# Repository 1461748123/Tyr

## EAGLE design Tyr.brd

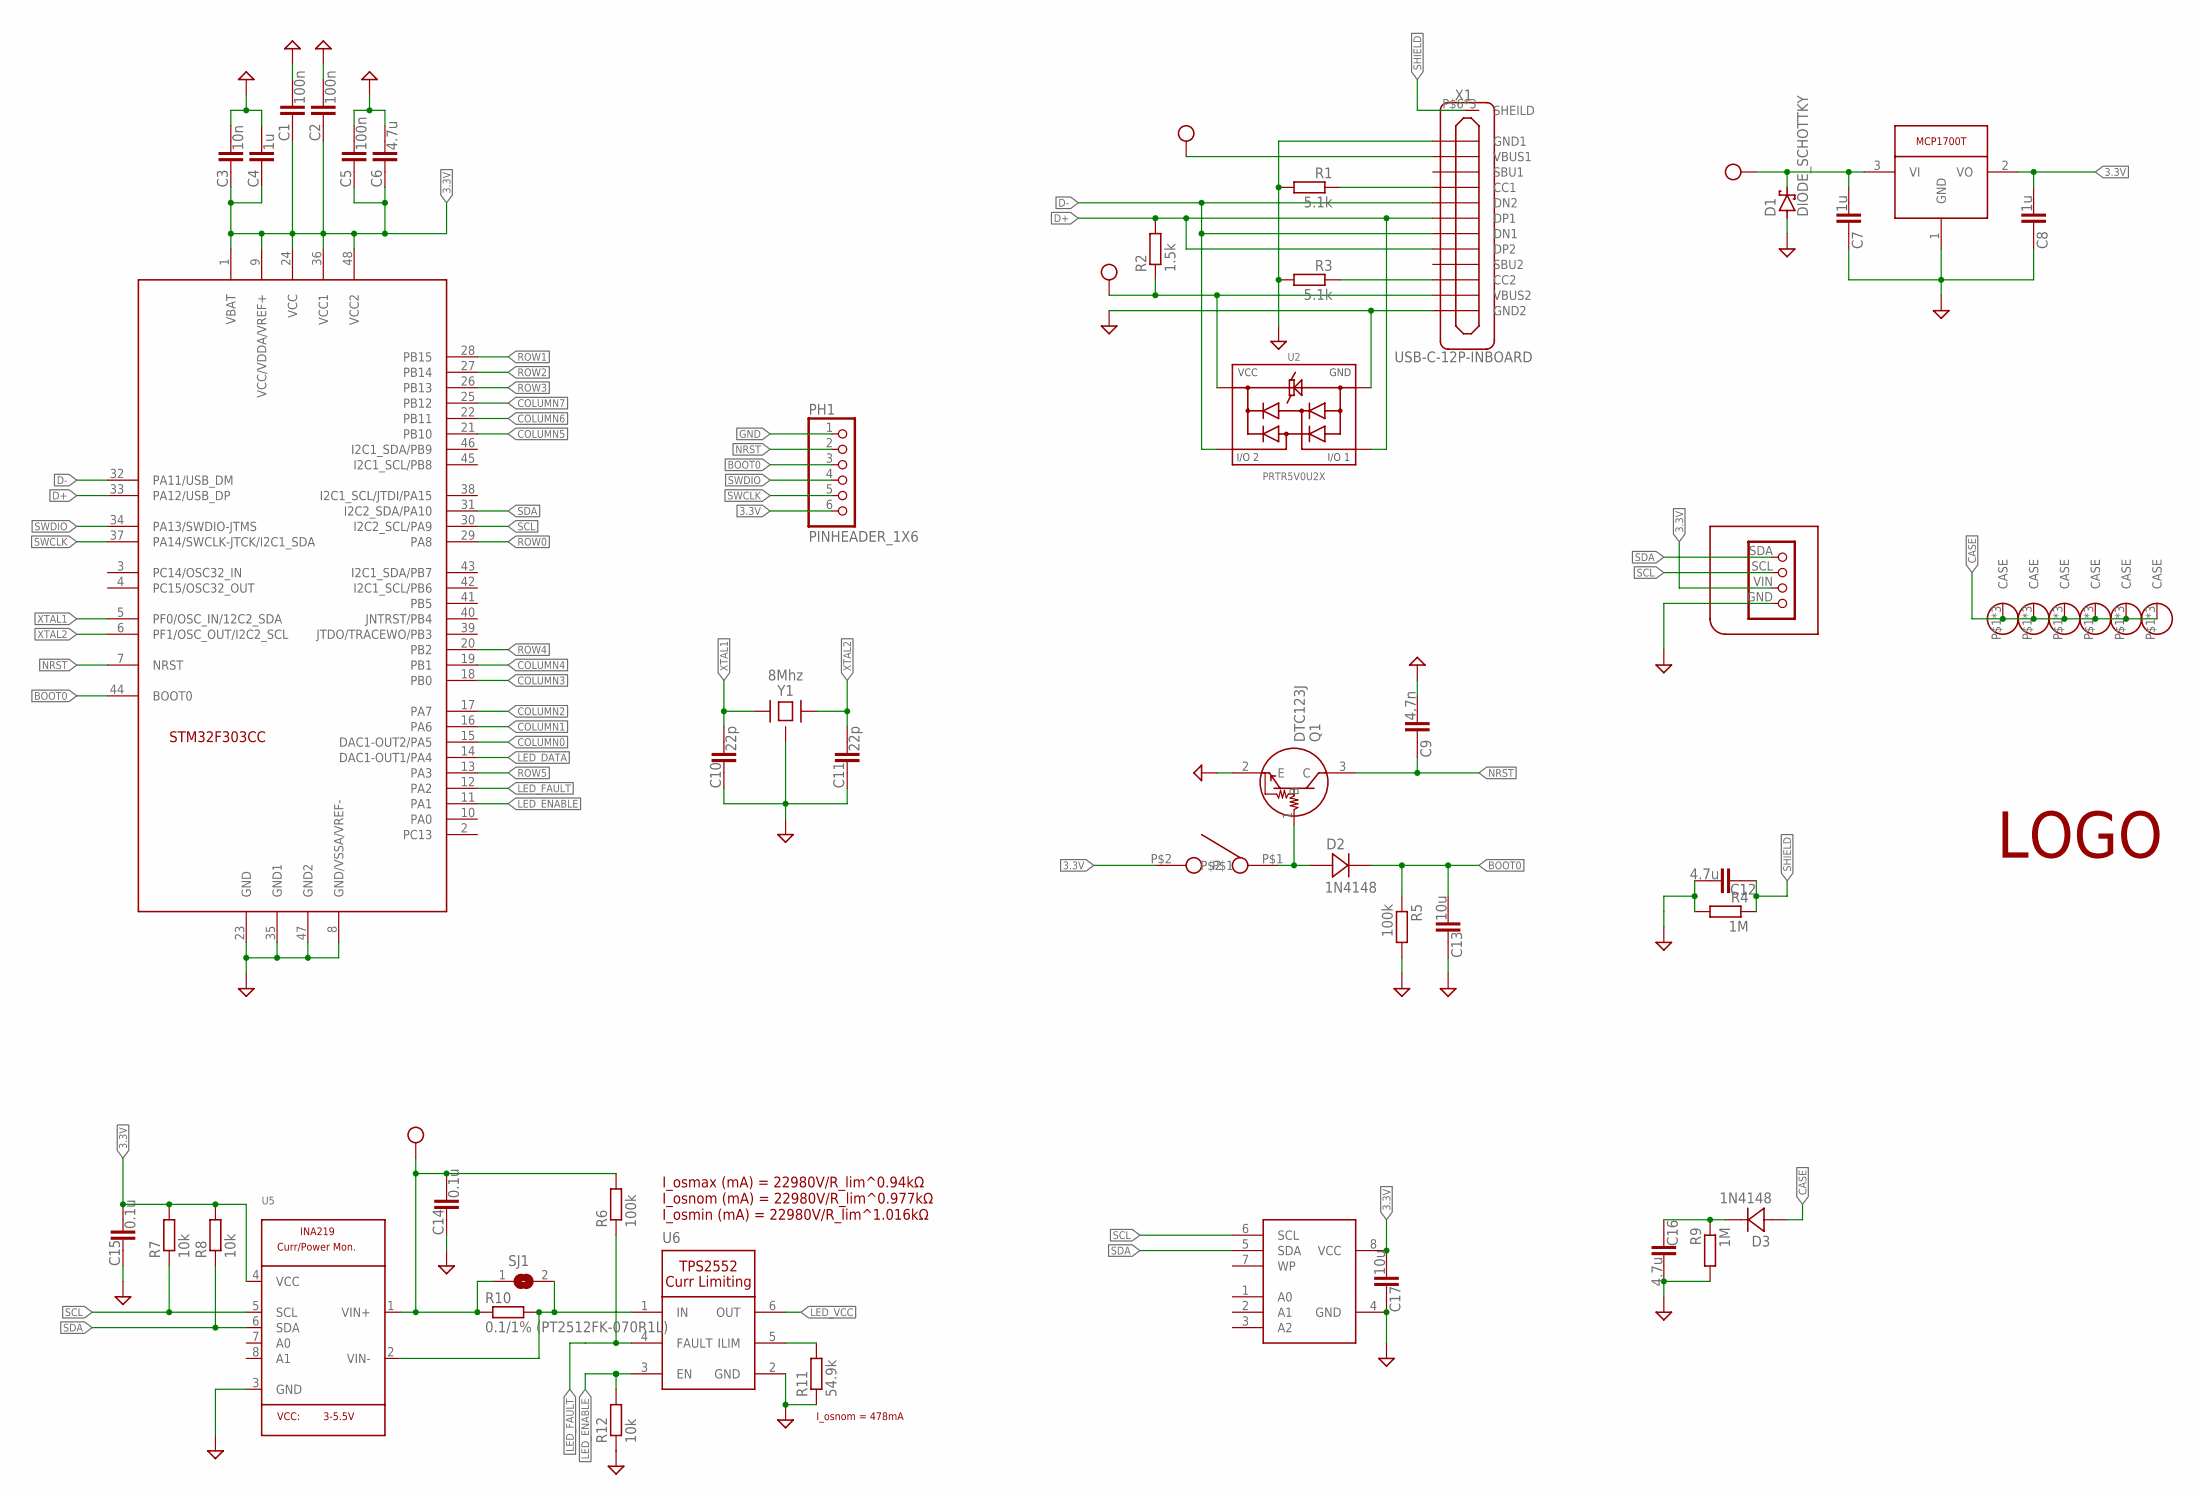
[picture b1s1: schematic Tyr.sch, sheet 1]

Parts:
C1, C2, C5: 100n; C0603
C3: 10n; C0603
C4, C7, C8: 1u; C0603
C6, C12, C16: 4.7u; C0603
C9: 4.7n; C0603
C10, C11: 22p; C0603
C13, C17: 10u; C0603
C14, C15: 0.1u; C0603
D1: DIODE_SCHOTTKY; SOD-123
D2, D3: 1N4148; SOD-123
HOLE1, HOLE2: MOUNT_HOLE-5MM_NOTCH; HOLE_5MM_OVAL
HOLE3, HOLE4, HOLE5, HOLE6: MOUNT_HOLE; HOLE_M3_OVAL
J1: TYR_DISPLAY; TYR_TYR_DISPLAY
LOGO1: LOGO_TYR; LOGO_TYR_COPPER
PH1: PINHEADER_1X6; 1X06
Q1: DTC123J; SOT-323
R1, R3: 5.1k; R0603
R2: 1.5k; R0603
R4, R9: 1M; R0603
R5, R6: 100k; R0603
R7, R8, R12: 10k; R0603
R10: 0.1/1% (PT2512FK-070R1L); R2512
R11: 54.9k; R0603
SJ1: SOLDERJUMPER; SOLDERJUMPER_ARROW_NOPASTE
SW1: BUTTON; BUTTON_3*6*2.5
U1: MCP1700T; SOT-23
U2: PRTR5V0U2X
U3: STM32F303CC; LQFP48
U4: MB85RC256V; SOP-8
U5: INA219; SOT23-8
U6: TPS2552; SOT-23-6P
X1: USB-C-12P-INBOARD
Y1: 8Mhz; CRYSTAL-3.2X2.5

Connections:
3.3V: C1.1, C2.1, C3.1, C4.1, C5.1, C6.1, C8.2, C15.2, C17.2, J1.VIN (4), PH1.6, R7.2, R8.2, SW1.P$2, U1.2 (VO), U3.1 (VBAT), U3.9 (VCC/VDDA/VREF+), U3.24 (VCC), U3.36 (VCC1), U3.48 (VCC2), U4.8 (VCC), U5.4 (VCC)
BOOT0: C13.2, D2.C, PH1.3, R5.1, U3.44 (BOOT0)
CASE: D3.A, HOLE1.P$1, HOLE1.P$2, HOLE1.P$3, HOLE2.P$1, HOLE2.P$2, HOLE2.P$3, HOLE3.P$1, HOLE3.P$2, HOLE3.P$3, HOLE4.P$1, HOLE4.P$2, HOLE4.P$3, HOLE5.P$1, HOLE5.P$2, HOLE5.P$3, HOLE6.P$1, HOLE6.P$2, HOLE6.P$3
COLUMN0: U3.15 (DAC1-OUT2/PA5); also elsewhere on the board
COLUMN1: U3.16 (PA6); also elsewhere on the board
COLUMN2: U3.17 (PA7); also elsewhere on the board
COLUMN3: U3.18 (PB0); also elsewhere on the board
COLUMN4: U3.19 (PB1); also elsewhere on the board
COLUMN5: U3.21 (PB10); also elsewhere on the board
COLUMN6: U3.22 (PB11); also elsewhere on the board
COLUMN7: U3.25 (PB12); also elsewhere on the board
D+: R2.2, U2.2, U3.33 (PA12/USB_DP), X1.DP1, X1.DP2
D-: U2.3, U3.32 (PA11/USB_DM), X1.DN1, X1.DN2
GND: C1.2, C2.2, C3.2, C4.2, C5.2, C6.2, C7.1, C8.1, C9.2, C10.1, C11.1, C12.2, C13.1, C14.1, C15.1, C16.2, C17.1, D1.A, J1.GND (3), PH1.1, Q1.2 (E), R1.2, R3.2, R4.2, R5.2, R9.2, R11.1, R12.1, U1.1 (GND), U2.1, U3.8 (GND/VSSA/VREF-), U3.23 (GND), U3.35 (GND1), U3.47 (GND2), U4.4 (GND), U5.3 (GND), U6.2 (GND), X1.GND1, X1.GND2, Y1.2 (GND), Y1.4 (GND); also elsewhere on the board
LED_DATA: U3.14 (DAC1-OUT1/PA4); also elsewhere on the board
LED_ENABLE: R12.2, U3.11 (PA1), U6.3 (EN)
LED_FAULT: R6.1, U3.12 (PA2), U6.4 (FAULT)
LED_VCC: U6.6 (OUT); also elsewhere on the board
unnamed: R10.2, SJ1.2, U5.2 (VIN-), U6.1 (IN)
unnamed: R11.2, U6.5 (ILIM)
unnamed: R1.1, X1.CC1
unnamed: D2.A, Q1.1 (B), SW1.P$1
unnamed: C16.1, D3.C, R9.1
unnamed: R3.1, X1.CC2
NRST: C9.1, PH1.2, Q1.3 (C), U3.7 (NRST)
ROW0: U3.29 (PA8); also elsewhere on the board
ROW1: U3.28 (PB15); also elsewhere on the board
ROW2: U3.27 (PB14); also elsewhere on the board
ROW3: U3.26 (PB13); also elsewhere on the board
ROW4: U3.20 (PB2); also elsewhere on the board
ROW5: U3.13 (PA3); also elsewhere on the board
SCL: J1.SCL (2), R7.1, U3.30 (I2C2_SCL/PA9), U4.6 (SCL), U5.5 (SCL)
SDA: J1.SDA (1), R8.1, U3.31 (I2C2_SDA/PA10), U4.5 (SDA), U5.6 (SDA)
SHIELD: C12.1, R4.1, X1.P$6 (SHEILD), X1.P$9 (SHEILD), X1.P$12 (SHEILD)
SWCLK: PH1.5, U3.37 (PA14/SWCLK-JTCK/I2C1_SDA)
SWDIO: PH1.4, U3.34 (PA13/SWDIO-JTMS)
VCC: C7.2, C14.2, D1.C, R2.1, R6.2, R10.1, SJ1.1, U1.3 (VI), U2.4, U5.1 (VIN+), X1.VBUS1, X1.VBUS2
XTAL1: C10.2, U3.5 (PF0/OSC_IN/12C2_SDA), Y1.1
XTAL2: C11.2, U3.6 (PF1/OSC_OUT/I2C2_SCL), Y1.3 (2)

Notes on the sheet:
I_osmax (mA) = 22980V/R_lim^0.94kΩ I_osnom (mA) = 22980V/R_lim^0.977kΩ I_osmin (mA) = 22980V/R_lim^1.016kΩ
I_osnom = 478mA

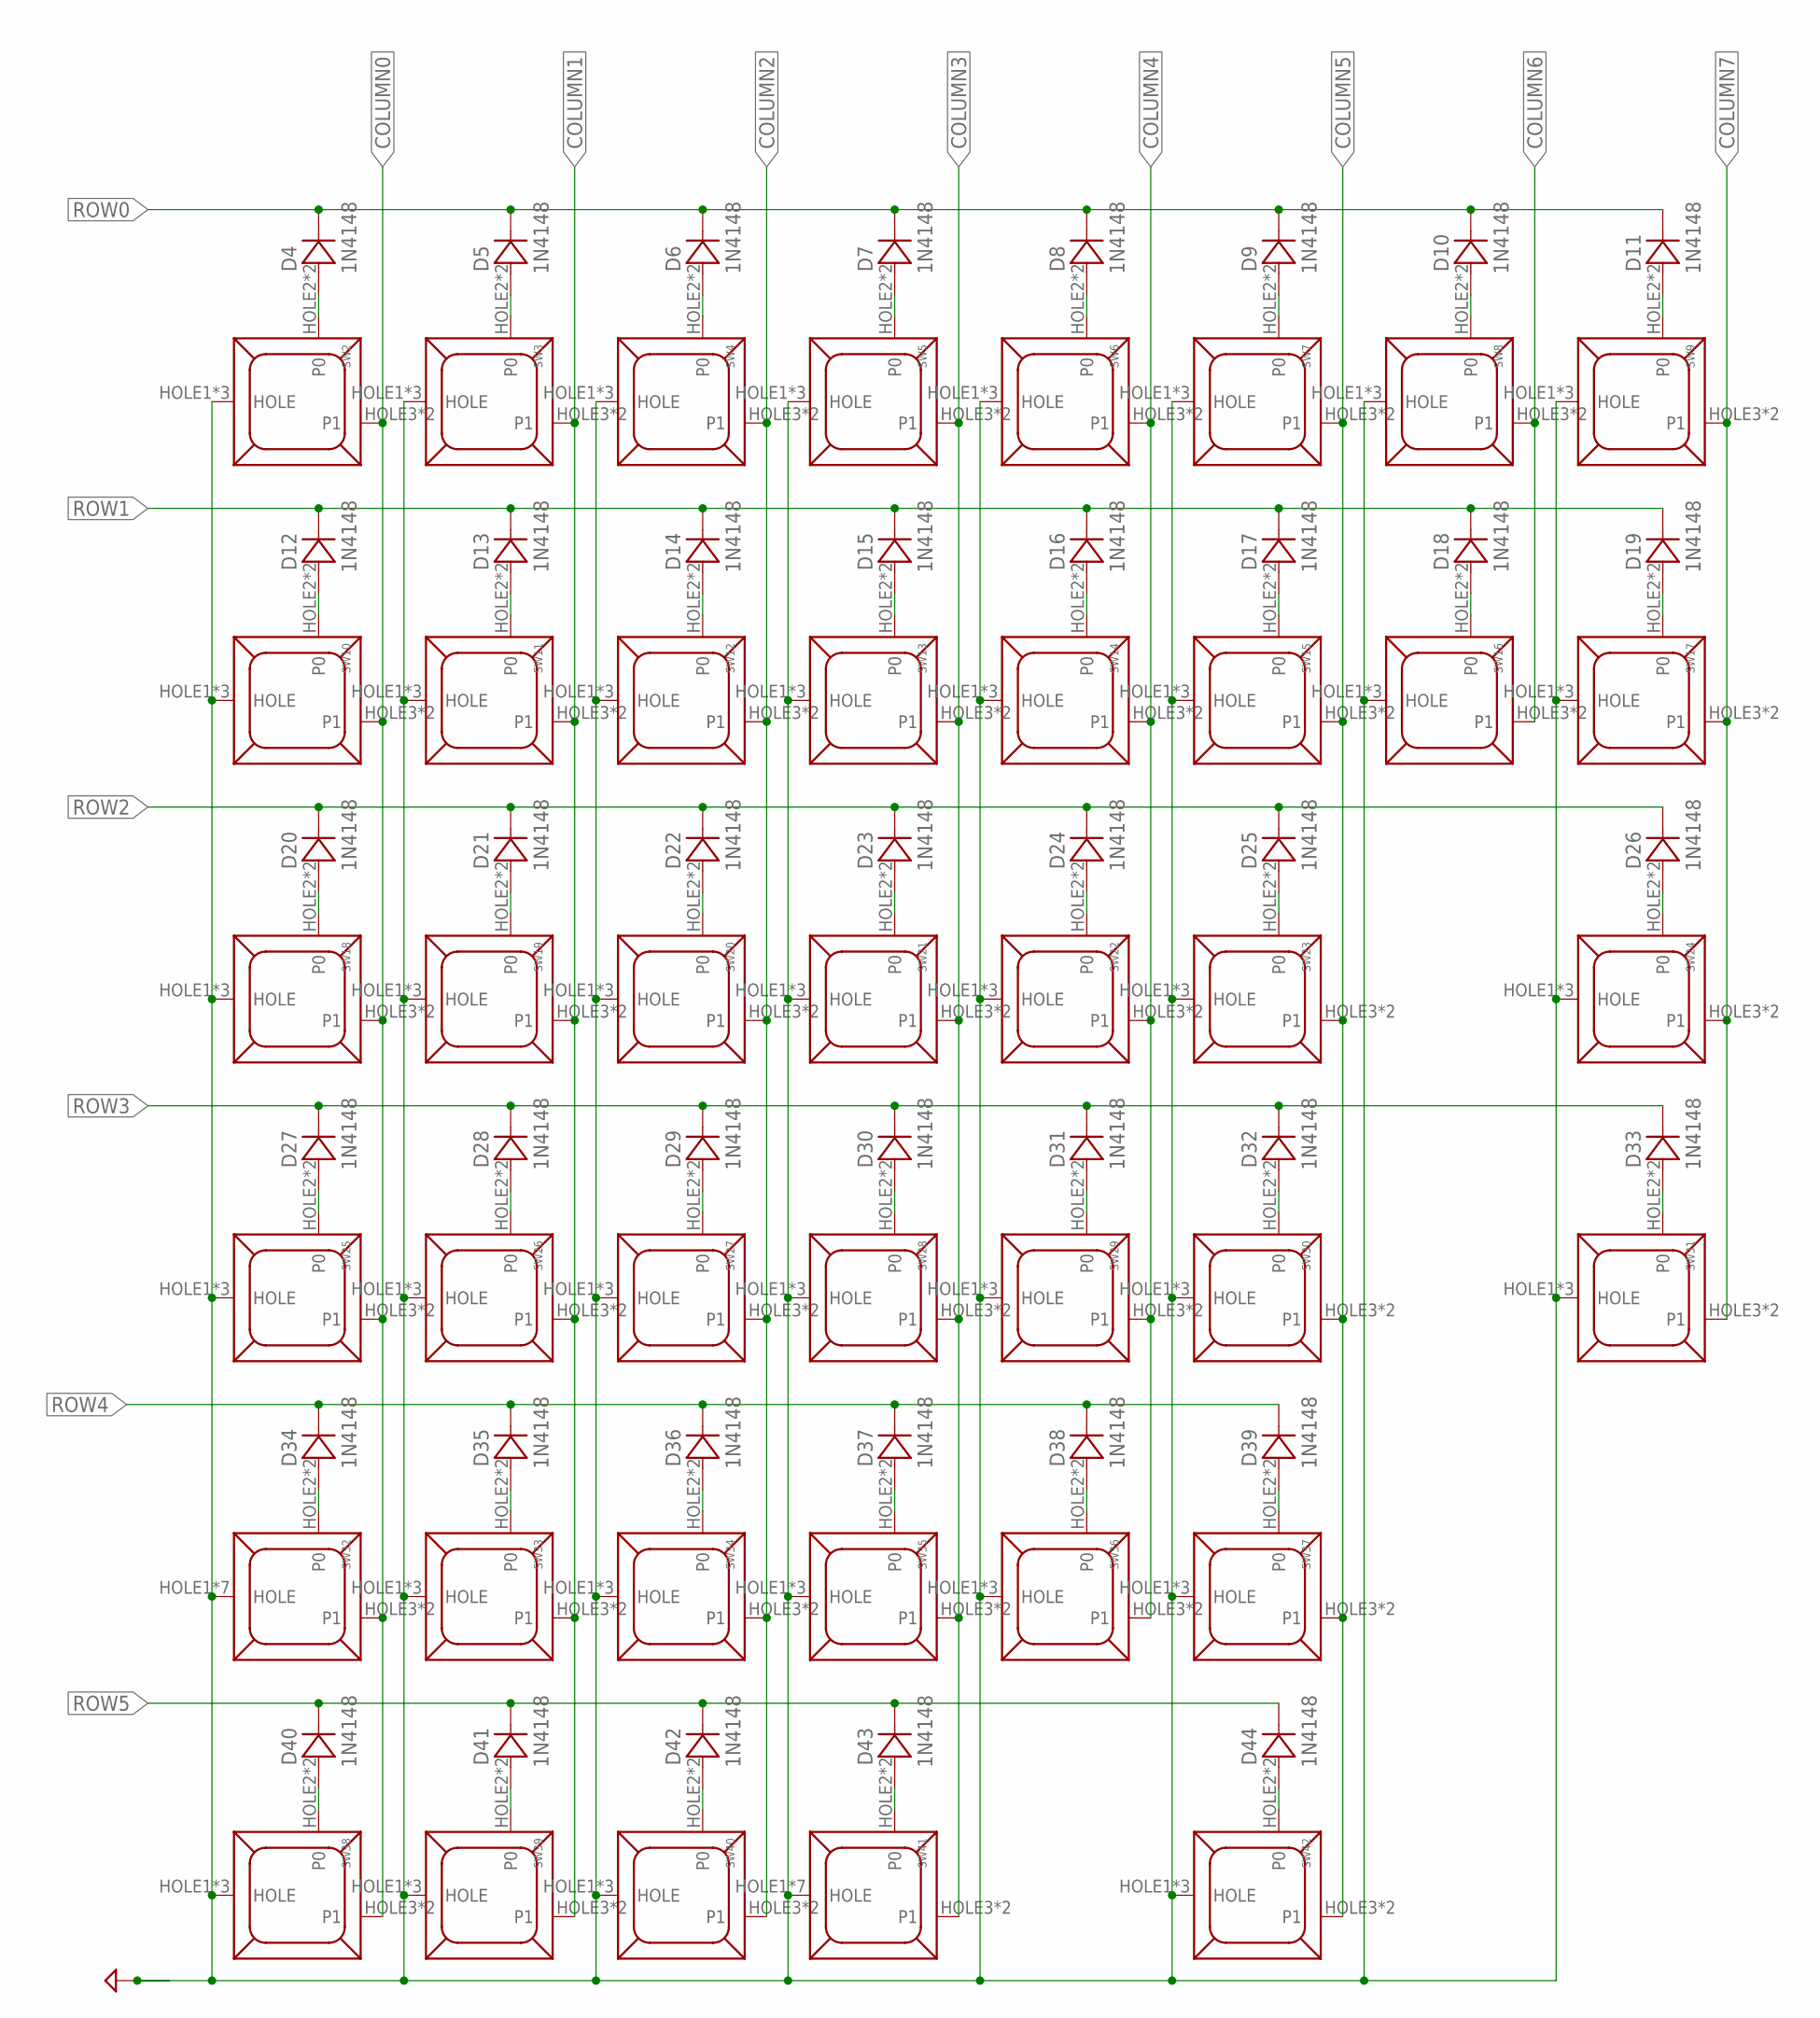
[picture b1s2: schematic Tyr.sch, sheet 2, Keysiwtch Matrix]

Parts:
D4, D5, D6, D7, D8, D9, D10, D11, D12, D13, D14, D15, D16, D17, D18, D19, D20, D21, D22, D23, D24, D25, D26, D27, D28, D29, D30, D31, D32, D33, D34, D35, D36, D37, D38, D39, D40, D41, D42, D43, D44: 1N4148; SOD-123
SW2, SW3, SW4, SW5, SW6, SW7, SW8, SW9, SW10, SW11, SW12, SW13, SW14, SW15, SW16, SW17, SW18, SW19, SW20, SW21, SW22, SW23, SW24, SW26, SW27, SW28, SW29, SW30, SW31, SW33, SW34, SW35, SW36, SW37, SW38, SW39, SW40, SW42: MX; MX-1U-HOTSWAP
SW25: MX; MX-1U-HOTSWAP-CAPSLOCK
SW32, SW41: MX; MX-2U-HOTSWAP

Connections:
COLUMN0: SW2.HOLE3 (P1), SW2.P$1 (P1), SW10.HOLE3 (P1), SW10.P$1 (P1), SW18.HOLE3 (P1), SW18.P$1 (P1), SW25.HOLE3 (P1), SW25.P$1 (P1), SW32.HOLE3 (P1), SW32.P$1 (P1), SW38.HOLE3 (P1), SW38.P$1 (P1); also elsewhere on the board
COLUMN1: SW3.HOLE3 (P1), SW3.P$1 (P1), SW11.HOLE3 (P1), SW11.P$1 (P1), SW19.HOLE3 (P1), SW19.P$1 (P1), SW26.HOLE3 (P1), SW26.P$1 (P1), SW33.HOLE3 (P1), SW33.P$1 (P1), SW39.HOLE3 (P1), SW39.P$1 (P1); also elsewhere on the board
COLUMN2: SW4.HOLE3 (P1), SW4.P$1 (P1), SW12.HOLE3 (P1), SW12.P$1 (P1), SW20.HOLE3 (P1), SW20.P$1 (P1), SW27.HOLE3 (P1), SW27.P$1 (P1), SW34.HOLE3 (P1), SW34.P$1 (P1), SW40.HOLE3 (P1), SW40.P$1 (P1); also elsewhere on the board
COLUMN3: SW5.HOLE3 (P1), SW5.P$1 (P1), SW13.HOLE3 (P1), SW13.P$1 (P1), SW21.HOLE3 (P1), SW21.P$1 (P1), SW28.HOLE3 (P1), SW28.P$1 (P1), SW35.HOLE3 (P1), SW35.P$1 (P1), SW41.HOLE3 (P1), SW41.P$1 (P1); also elsewhere on the board
COLUMN4: SW6.HOLE3 (P1), SW6.P$1 (P1), SW14.HOLE3 (P1), SW14.P$1 (P1), SW22.HOLE3 (P1), SW22.P$1 (P1), SW29.HOLE3 (P1), SW29.P$1 (P1), SW36.HOLE3 (P1), SW36.P$1 (P1); also elsewhere on the board
COLUMN5: SW7.HOLE3 (P1), SW7.P$1 (P1), SW15.HOLE3 (P1), SW15.P$1 (P1), SW23.HOLE3 (P1), SW23.P$1 (P1), SW30.HOLE3 (P1), SW30.P$1 (P1), SW37.HOLE3 (P1), SW37.P$1 (P1), SW42.HOLE3 (P1), SW42.P$1 (P1); also elsewhere on the board
COLUMN6: SW8.HOLE3 (P1), SW8.P$1 (P1), SW16.HOLE3 (P1), SW16.P$1 (P1); also elsewhere on the board
COLUMN7: SW9.HOLE3 (P1), SW9.P$1 (P1), SW17.HOLE3 (P1), SW17.P$1 (P1), SW24.HOLE3 (P1), SW24.P$1 (P1), SW31.HOLE3 (P1), SW31.P$1 (P1); also elsewhere on the board
GND: SW2.HOLE1 (HOLE), SW2.HOLE4 (HOLE), SW2.HOLE5 (HOLE), SW3.HOLE1 (HOLE), SW3.HOLE4 (HOLE), SW3.HOLE5 (HOLE), SW4.HOLE1 (HOLE), SW4.HOLE4 (HOLE), SW4.HOLE5 (HOLE), SW5.HOLE1 (HOLE), SW5.HOLE4 (HOLE), SW5.HOLE5 (HOLE), SW6.HOLE1 (HOLE), SW6.HOLE4 (HOLE), SW6.HOLE5 (HOLE), SW7.HOLE1 (HOLE), SW7.HOLE4 (HOLE), SW7.HOLE5 (HOLE), SW8.HOLE1 (HOLE), SW8.HOLE4 (HOLE), SW8.HOLE5 (HOLE), SW9.HOLE1 (HOLE), SW9.HOLE4 (HOLE), SW9.HOLE5 (HOLE), SW10.HOLE1 (HOLE), SW10.HOLE4 (HOLE), SW10.HOLE5 (HOLE), SW11.HOLE1 (HOLE), SW11.HOLE4 (HOLE), SW11.HOLE5 (HOLE), SW12.HOLE1 (HOLE), SW12.HOLE4 (HOLE), SW12.HOLE5 (HOLE), SW13.HOLE1 (HOLE), SW13.HOLE4 (HOLE), SW13.HOLE5 (HOLE), SW14.HOLE1 (HOLE), SW14.HOLE4 (HOLE), SW14.HOLE5 (HOLE), SW15.HOLE1 (HOLE), SW15.HOLE4 (HOLE), SW15.HOLE5 (HOLE), SW16.HOLE1 (HOLE), SW16.HOLE4 (HOLE), SW16.HOLE5 (HOLE), SW17.HOLE1 (HOLE), SW17.HOLE4 (HOLE), SW17.HOLE5 (HOLE), SW18.HOLE1 (HOLE), SW18.HOLE4 (HOLE), SW18.HOLE5 (HOLE), SW19.HOLE1 (HOLE), SW19.HOLE4 (HOLE), SW19.HOLE5 (HOLE), SW20.HOLE1 (HOLE), SW20.HOLE4 (HOLE), SW20.HOLE5 (HOLE), SW21.HOLE1 (HOLE), SW21.HOLE4 (HOLE), SW21.HOLE5 (HOLE), SW22.HOLE1 (HOLE), SW22.HOLE4 (HOLE), SW22.HOLE5 (HOLE), SW23.HOLE1 (HOLE), SW23.HOLE4 (HOLE), SW23.HOLE5 (HOLE), SW24.HOLE1 (HOLE), SW24.HOLE4 (HOLE), SW24.HOLE5 (HOLE), SW25.HOLE1 (HOLE), SW25.HOLE4 (HOLE), SW25.HOLE5 (HOLE), SW26.HOLE1 (HOLE), SW26.HOLE4 (HOLE), SW26.HOLE5 (HOLE), SW27.HOLE1 (HOLE), SW27.HOLE4 (HOLE), SW27.HOLE5 (HOLE), SW28.HOLE1 (HOLE), SW28.HOLE4 (HOLE), SW28.HOLE5 (HOLE), SW29.HOLE1 (HOLE), SW29.HOLE4 (HOLE), SW29.HOLE5 (HOLE), SW30.HOLE1 (HOLE), SW30.HOLE4 (HOLE), SW30.HOLE5 (HOLE), SW31.HOLE1 (HOLE), SW31.HOLE4 (HOLE), SW31.HOLE5 (HOLE), SW32.HOLE1 (HOLE), SW32.HOLE4 (HOLE), SW32.HOLE5 (HOLE), SW32.HOLE6 (HOLE), SW32.HOLE7 (HOLE), SW32.HOLE8 (HOLE), SW32.HOLE9 (HOLE), SW33.HOLE1 (HOLE), SW33.HOLE4 (HOLE), SW33.HOLE5 (HOLE), SW34.HOLE1 (HOLE), SW34.HOLE4 (HOLE), SW34.HOLE5 (HOLE), SW35.HOLE1 (HOLE), SW35.HOLE4 (HOLE), SW35.HOLE5 (HOLE), SW36.HOLE1 (HOLE), SW36.HOLE4 (HOLE), SW36.HOLE5 (HOLE), SW37.HOLE1 (HOLE), SW37.HOLE4 (HOLE), SW37.HOLE5 (HOLE), SW38.HOLE1 (HOLE), SW38.HOLE4 (HOLE), SW38.HOLE5 (HOLE), SW39.HOLE1 (HOLE), SW39.HOLE4 (HOLE), SW39.HOLE5 (HOLE), SW40.HOLE1 (HOLE), SW40.HOLE4 (HOLE), SW40.HOLE5 (HOLE), SW41.HOLE1 (HOLE), SW41.HOLE4 (HOLE), SW41.HOLE5 (HOLE), SW41.HOLE6 (HOLE), SW41.HOLE7 (HOLE), SW41.HOLE8 (HOLE), SW41.HOLE9 (HOLE), SW42.HOLE1 (HOLE), SW42.HOLE4 (HOLE), SW42.HOLE5 (HOLE); also elsewhere on the board
unnamed: D13.A, SW11.HOLE2 (P0), SW11.P$2 (P0)
unnamed: D4.A, SW2.HOLE2 (P0), SW2.P$2 (P0)
unnamed: D5.A, SW3.HOLE2 (P0), SW3.P$2 (P0)
unnamed: D6.A, SW4.HOLE2 (P0), SW4.P$2 (P0)
unnamed: D7.A, SW5.HOLE2 (P0), SW5.P$2 (P0)
unnamed: D8.A, SW6.HOLE2 (P0), SW6.P$2 (P0)
unnamed: D9.A, SW7.HOLE2 (P0), SW7.P$2 (P0)
unnamed: D10.A, SW8.HOLE2 (P0), SW8.P$2 (P0)
unnamed: D11.A, SW9.HOLE2 (P0), SW9.P$2 (P0)
unnamed: D19.A, SW17.HOLE2 (P0), SW17.P$2 (P0)
unnamed: D18.A, SW16.HOLE2 (P0), SW16.P$2 (P0)
unnamed: D17.A, SW15.HOLE2 (P0), SW15.P$2 (P0)
unnamed: D16.A, SW14.HOLE2 (P0), SW14.P$2 (P0)
unnamed: D15.A, SW13.HOLE2 (P0), SW13.P$2 (P0)
unnamed: D14.A, SW12.HOLE2 (P0), SW12.P$2 (P0)
unnamed: D12.A, SW10.HOLE2 (P0), SW10.P$2 (P0)
unnamed: D26.A, SW24.HOLE2 (P0), SW24.P$2 (P0)
unnamed: D25.A, SW23.HOLE2 (P0), SW23.P$2 (P0)
unnamed: D24.A, SW22.HOLE2 (P0), SW22.P$2 (P0)
unnamed: D23.A, SW21.HOLE2 (P0), SW21.P$2 (P0)
unnamed: D22.A, SW20.HOLE2 (P0), SW20.P$2 (P0)
unnamed: D20.A, SW18.HOLE2 (P0), SW18.P$2 (P0)
unnamed: D27.A, SW25.HOLE2 (P0), SW25.P$2 (P0)
unnamed: D28.A, SW26.HOLE2 (P0), SW26.P$2 (P0)
unnamed: D29.A, SW27.HOLE2 (P0), SW27.P$2 (P0)
unnamed: D30.A, SW28.HOLE2 (P0), SW28.P$2 (P0)
unnamed: D31.A, SW29.HOLE2 (P0), SW29.P$2 (P0)
unnamed: D32.A, SW30.HOLE2 (P0), SW30.P$2 (P0)
unnamed: D33.A, SW31.HOLE2 (P0), SW31.P$2 (P0)
unnamed: D39.A, SW37.HOLE2 (P0), SW37.P$2 (P0)
unnamed: D37.A, SW35.HOLE2 (P0), SW35.P$2 (P0)
unnamed: D36.A, SW34.HOLE2 (P0), SW34.P$2 (P0)
unnamed: D35.A, SW33.HOLE2 (P0), SW33.P$2 (P0)
unnamed: D34.A, SW32.HOLE2 (P0), SW32.P$2 (P0)
unnamed: D40.A, SW38.HOLE2 (P0), SW38.P$2 (P0)
unnamed: D41.A, SW39.HOLE2 (P0), SW39.P$2 (P0)
unnamed: D42.A, SW40.HOLE2 (P0), SW40.P$2 (P0)
unnamed: D43.A, SW41.HOLE2 (P0), SW41.P$2 (P0)
unnamed: D44.A, SW42.HOLE2 (P0), SW42.P$2 (P0)
unnamed: D38.A, SW36.HOLE2 (P0), SW36.P$2 (P0)
unnamed: D21.A, SW19.HOLE2 (P0), SW19.P$2 (P0)
ROW0: D4.C, D5.C, D6.C, D7.C, D8.C, D9.C, D10.C, D11.C; also elsewhere on the board
ROW1: D12.C, D13.C, D14.C, D15.C, D16.C, D17.C, D18.C, D19.C; also elsewhere on the board
ROW2: D20.C, D21.C, D22.C, D23.C, D24.C, D25.C, D26.C; also elsewhere on the board
ROW3: D27.C, D28.C, D29.C, D30.C, D31.C, D32.C, D33.C; also elsewhere on the board
ROW4: D34.C, D35.C, D36.C, D37.C, D38.C, D39.C; also elsewhere on the board
ROW5: D40.C, D41.C, D42.C, D43.C, D44.C; also elsewhere on the board

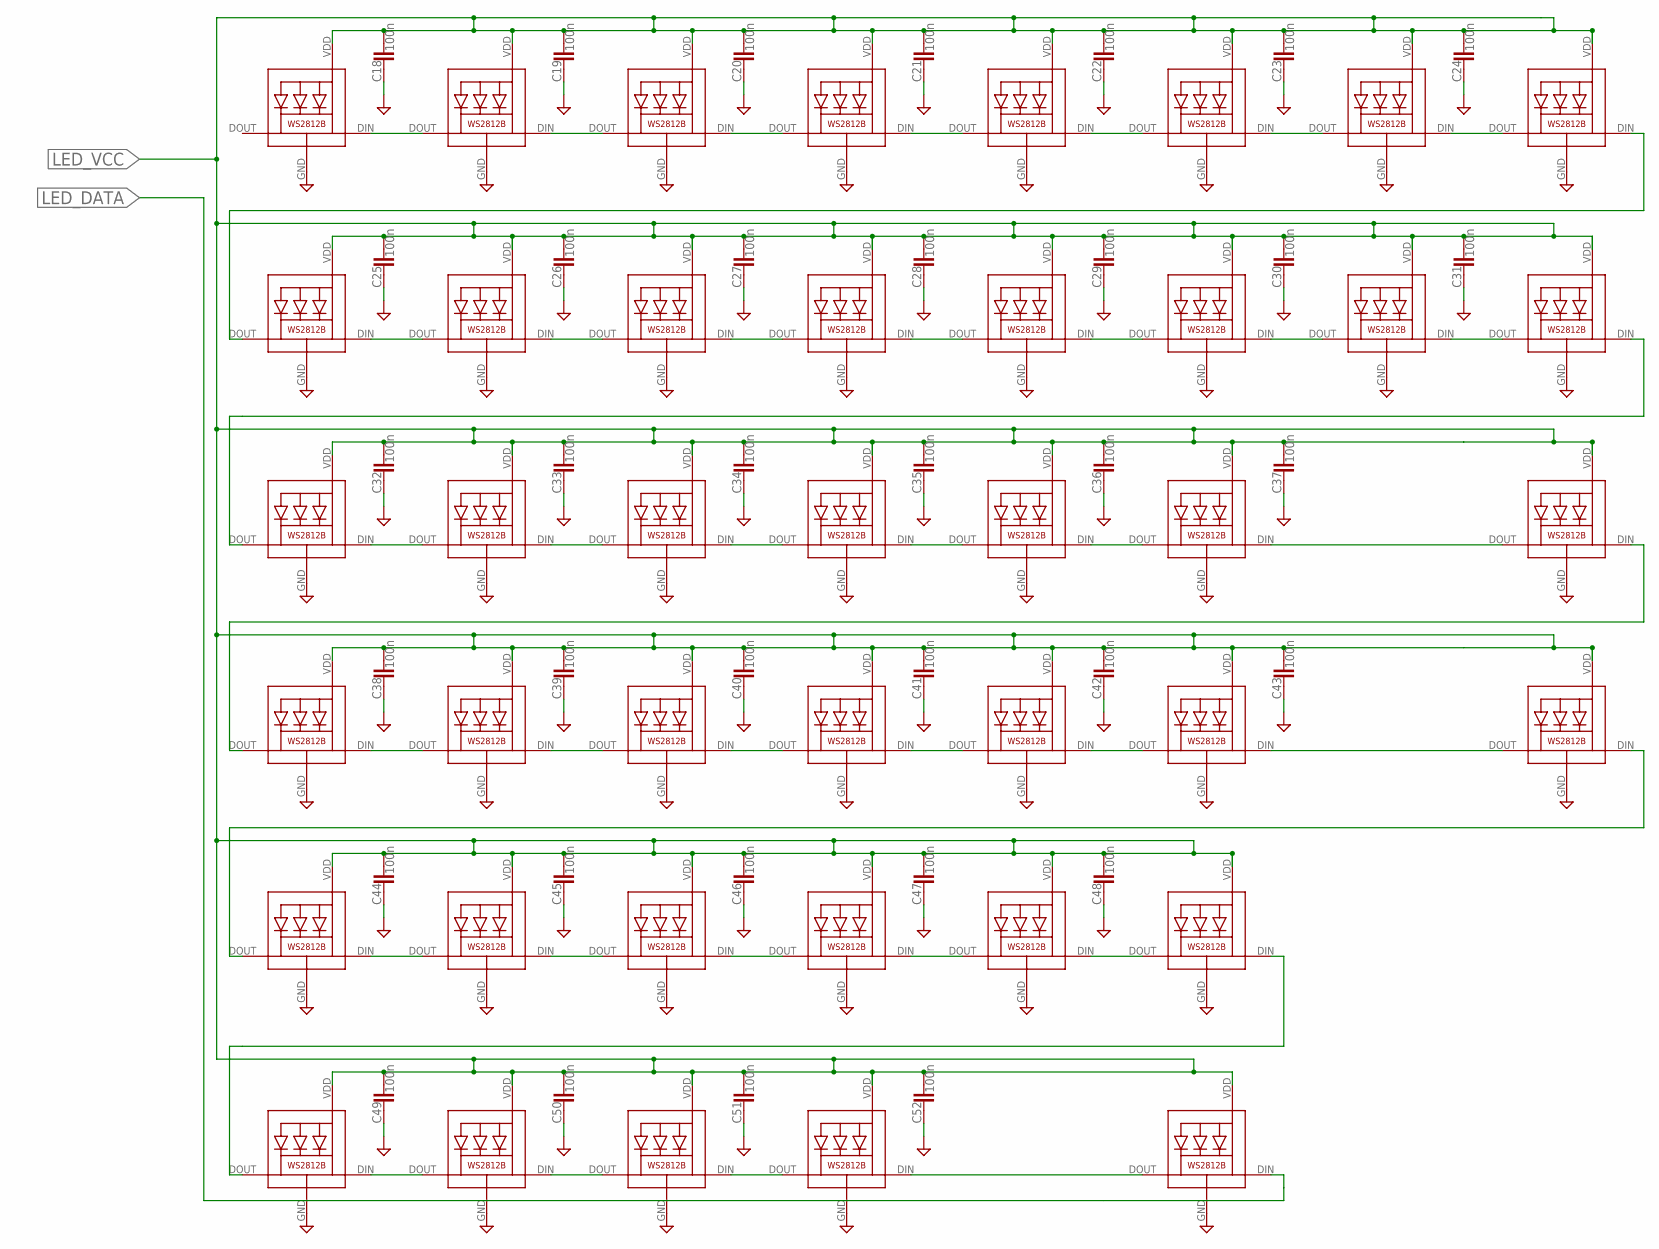
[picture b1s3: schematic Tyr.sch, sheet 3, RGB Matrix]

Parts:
C18, C19, C20, C21, C22, C23, C24, C25, C26, C27, C28, C29, C30, C31, C32, C33, C34, C35, C36, C37, C38, C39, C40, C41, C42, C43, C44, C45, C46, C47, C48, C49, C50, C51, C52: 100n; C0603
LED1, LED2, LED3, LED4, LED5, LED6, LED7, LED8, LED9, LED10, LED11, LED12, LED13, LED14, LED15, LED16, LED17, LED18, LED19, LED20, LED21, LED22, LED23, LED24, LED25, LED26, LED27, LED28, LED29, LED30, LED31, LED32, LED33, LED34, LED35, LED36, LED37, LED38, LED39, LED40, LED41: WS2812B_3528_REVERS-MOUNT

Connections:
GND: C18.1, C19.1, C20.1, C21.1, C22.1, C23.1, C24.1, C25.1, C26.1, C27.1, C28.1, C29.1, C30.1, C31.1, C32.1, C33.1, C34.1, C35.1, C36.1, C37.1, C38.1, C39.1, C40.1, C41.1, C42.1, C43.1, C44.1, C45.1, C46.1, C47.1, C48.1, C49.1, C50.1, C51.1, C52.1, LED1.GND, LED2.GND, LED3.GND, LED4.GND, LED5.GND, LED6.GND, LED7.GND, LED8.GND, LED9.GND, LED10.GND, LED11.GND, LED12.GND, LED13.GND, LED14.GND, LED15.GND, LED16.GND, LED17.GND, LED18.GND, LED19.GND, LED20.GND, LED21.GND, LED22.GND, LED23.GND, LED24.GND, LED25.GND, LED26.GND, LED27.GND, LED28.GND, LED29.GND, LED30.GND, LED31.GND, LED32.GND, LED33.GND, LED34.GND, LED35.GND, LED36.GND, LED37.GND, LED38.GND, LED39.GND, LED40.GND, LED41.GND; also elsewhere on the board
LED_DATA: LED41.DIN (DI); also elsewhere on the board
LED_VCC: C18.2, C19.2, C20.2, C21.2, C22.2, C23.2, C24.2, C25.2, C26.2, C27.2, C28.2, C29.2, C30.2, C31.2, C32.2, C33.2, C34.2, C35.2, C36.2, C37.2, C38.2, C39.2, C40.2, C41.2, C42.2, C43.2, C44.2, C45.2, C46.2, C47.2, C48.2, C49.2, C50.2, C51.2, C52.2, LED1.VDD, LED2.VDD, LED3.VDD, LED4.VDD, LED5.VDD, LED6.VDD, LED7.VDD, LED8.VDD, LED9.VDD, LED10.VDD, LED11.VDD, LED12.VDD, LED13.VDD, LED14.VDD, LED15.VDD, LED16.VDD, LED17.VDD, LED18.VDD, LED19.VDD, LED20.VDD, LED21.VDD, LED22.VDD, LED23.VDD, LED24.VDD, LED25.VDD, LED26.VDD, LED27.VDD, LED28.VDD, LED29.VDD, LED30.VDD, LED31.VDD, LED32.VDD, LED33.VDD, LED34.VDD, LED35.VDD, LED36.VDD, LED37.VDD, LED38.VDD, LED39.VDD, LED40.VDD, LED41.VDD; also elsewhere on the board
unnamed: LED40.DIN (DI), LED41.DOUT (DO)
unnamed: LED39.DIN (DI), LED40.DOUT (DO)
unnamed: LED38.DIN (DI), LED39.DOUT (DO)
unnamed: LED37.DIN (DI), LED38.DOUT (DO)
unnamed: LED36.DIN (DI), LED37.DOUT (DO)
unnamed: LED35.DIN (DI), LED36.DOUT (DO)
unnamed: LED34.DIN (DI), LED35.DOUT (DO)
unnamed: LED33.DIN (DI), LED34.DOUT (DO)
unnamed: LED32.DIN (DI), LED33.DOUT (DO)
unnamed: LED31.DIN (DI), LED32.DOUT (DO)
unnamed: LED30.DIN (DI), LED31.DOUT (DO)
unnamed: LED29.DIN (DI), LED30.DOUT (DO)
unnamed: LED28.DIN (DI), LED29.DOUT (DO)
unnamed: LED27.DIN (DI), LED28.DOUT (DO)
unnamed: LED26.DIN (DI), LED27.DOUT (DO)
unnamed: LED25.DIN (DI), LED26.DOUT (DO)
unnamed: LED24.DIN (DI), LED25.DOUT (DO)
unnamed: LED23.DIN (DI), LED24.DOUT (DO)
unnamed: LED22.DIN (DI), LED23.DOUT (DO)
unnamed: LED21.DIN (DI), LED22.DOUT (DO)
unnamed: LED20.DIN (DI), LED21.DOUT (DO)
unnamed: LED19.DIN (DI), LED20.DOUT (DO)
unnamed: LED18.DIN (DI), LED19.DOUT (DO)
unnamed: LED17.DIN (DI), LED18.DOUT (DO)
unnamed: LED16.DIN (DI), LED17.DOUT (DO)
unnamed: LED15.DIN (DI), LED16.DOUT (DO)
unnamed: LED14.DIN (DI), LED15.DOUT (DO)
unnamed: LED13.DIN (DI), LED14.DOUT (DO)
unnamed: LED12.DIN (DI), LED13.DOUT (DO)
unnamed: LED11.DIN (DI), LED12.DOUT (DO)
unnamed: LED10.DIN (DI), LED11.DOUT (DO)
unnamed: LED9.DIN (DI), LED10.DOUT (DO)
unnamed: LED8.DIN (DI), LED9.DOUT (DO)
unnamed: LED7.DIN (DI), LED8.DOUT (DO)
unnamed: LED6.DIN (DI), LED7.DOUT (DO)
unnamed: LED5.DIN (DI), LED6.DOUT (DO)
unnamed: LED4.DIN (DI), LED5.DOUT (DO)
unnamed: LED3.DIN (DI), LED4.DOUT (DO)
unnamed: LED2.DIN (DI), LED3.DOUT (DO)
unnamed: LED1.DIN (DI), LED2.DOUT (DO)

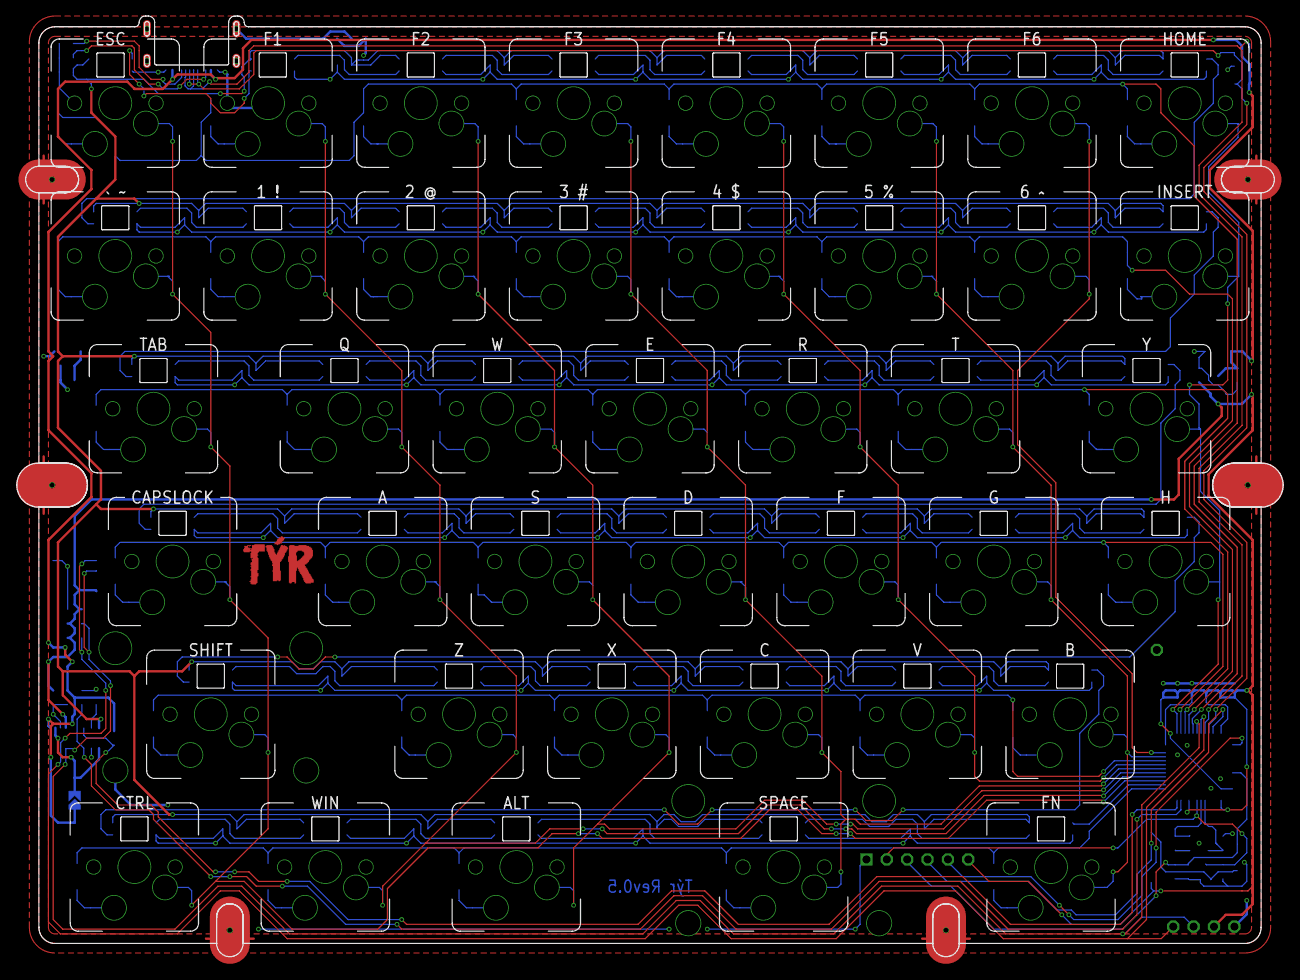
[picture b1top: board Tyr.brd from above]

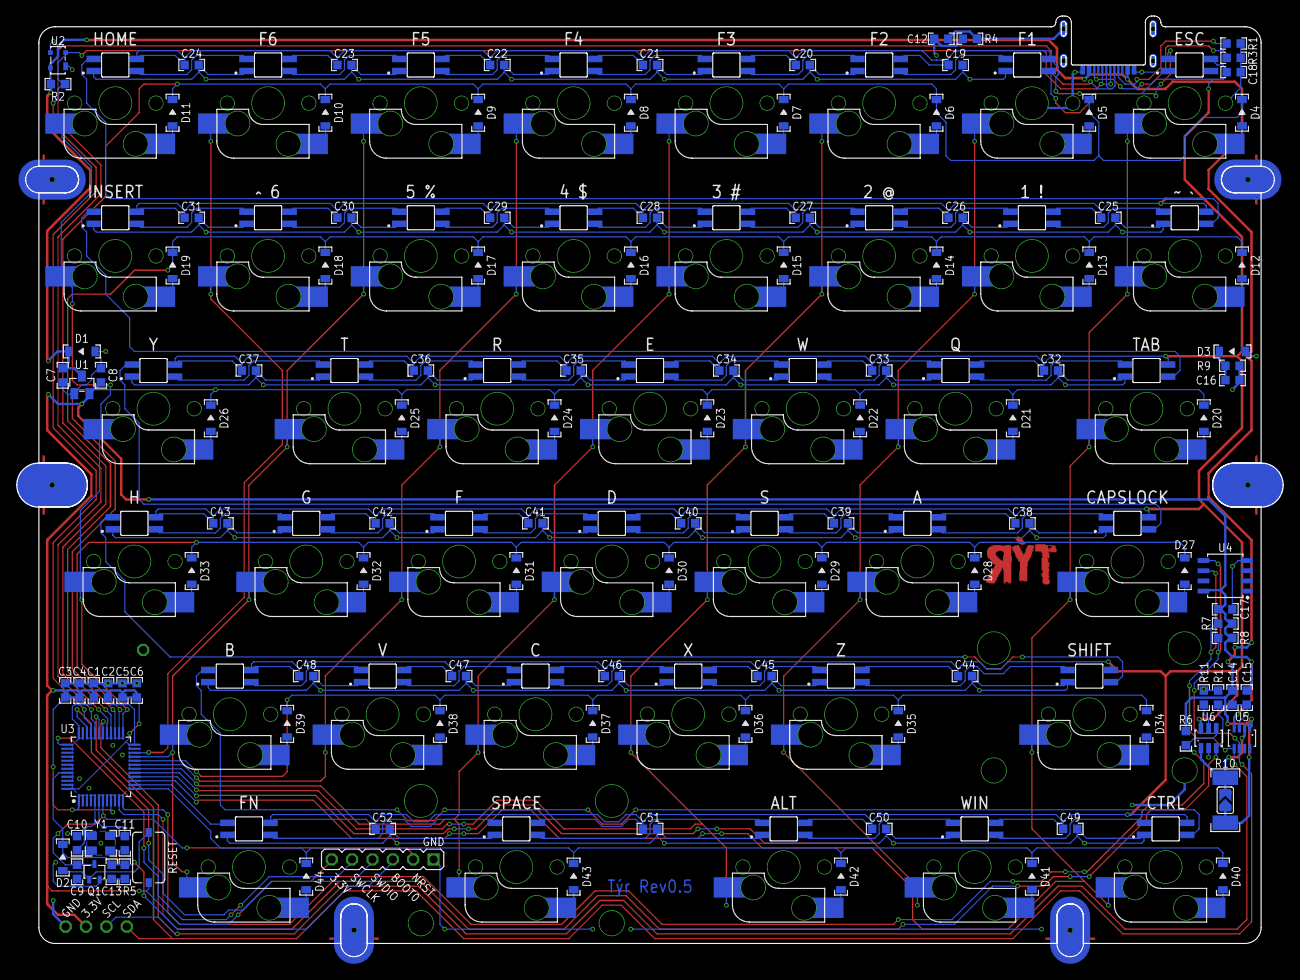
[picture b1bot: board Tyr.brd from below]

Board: 2 copper layers, 157.9 x 117.3 mm, 210 parts (161 on the bottom side), 120 nets.
